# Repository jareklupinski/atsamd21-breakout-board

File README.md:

# atsamd21-breakout-board
A Boilerplate for the ATSAMD21 microcontroller

The ATSAMD21 is one of my favorite microcontroller families. Its low cost and ease of programming made me want to create a board that suits my project needs, so it contains RTC circuitry, an SD card slot, and a few other helpful dev touches.

The board was produced, plugged in, and did not emit magic smoke. All of the functionality hasn't been tested yet.

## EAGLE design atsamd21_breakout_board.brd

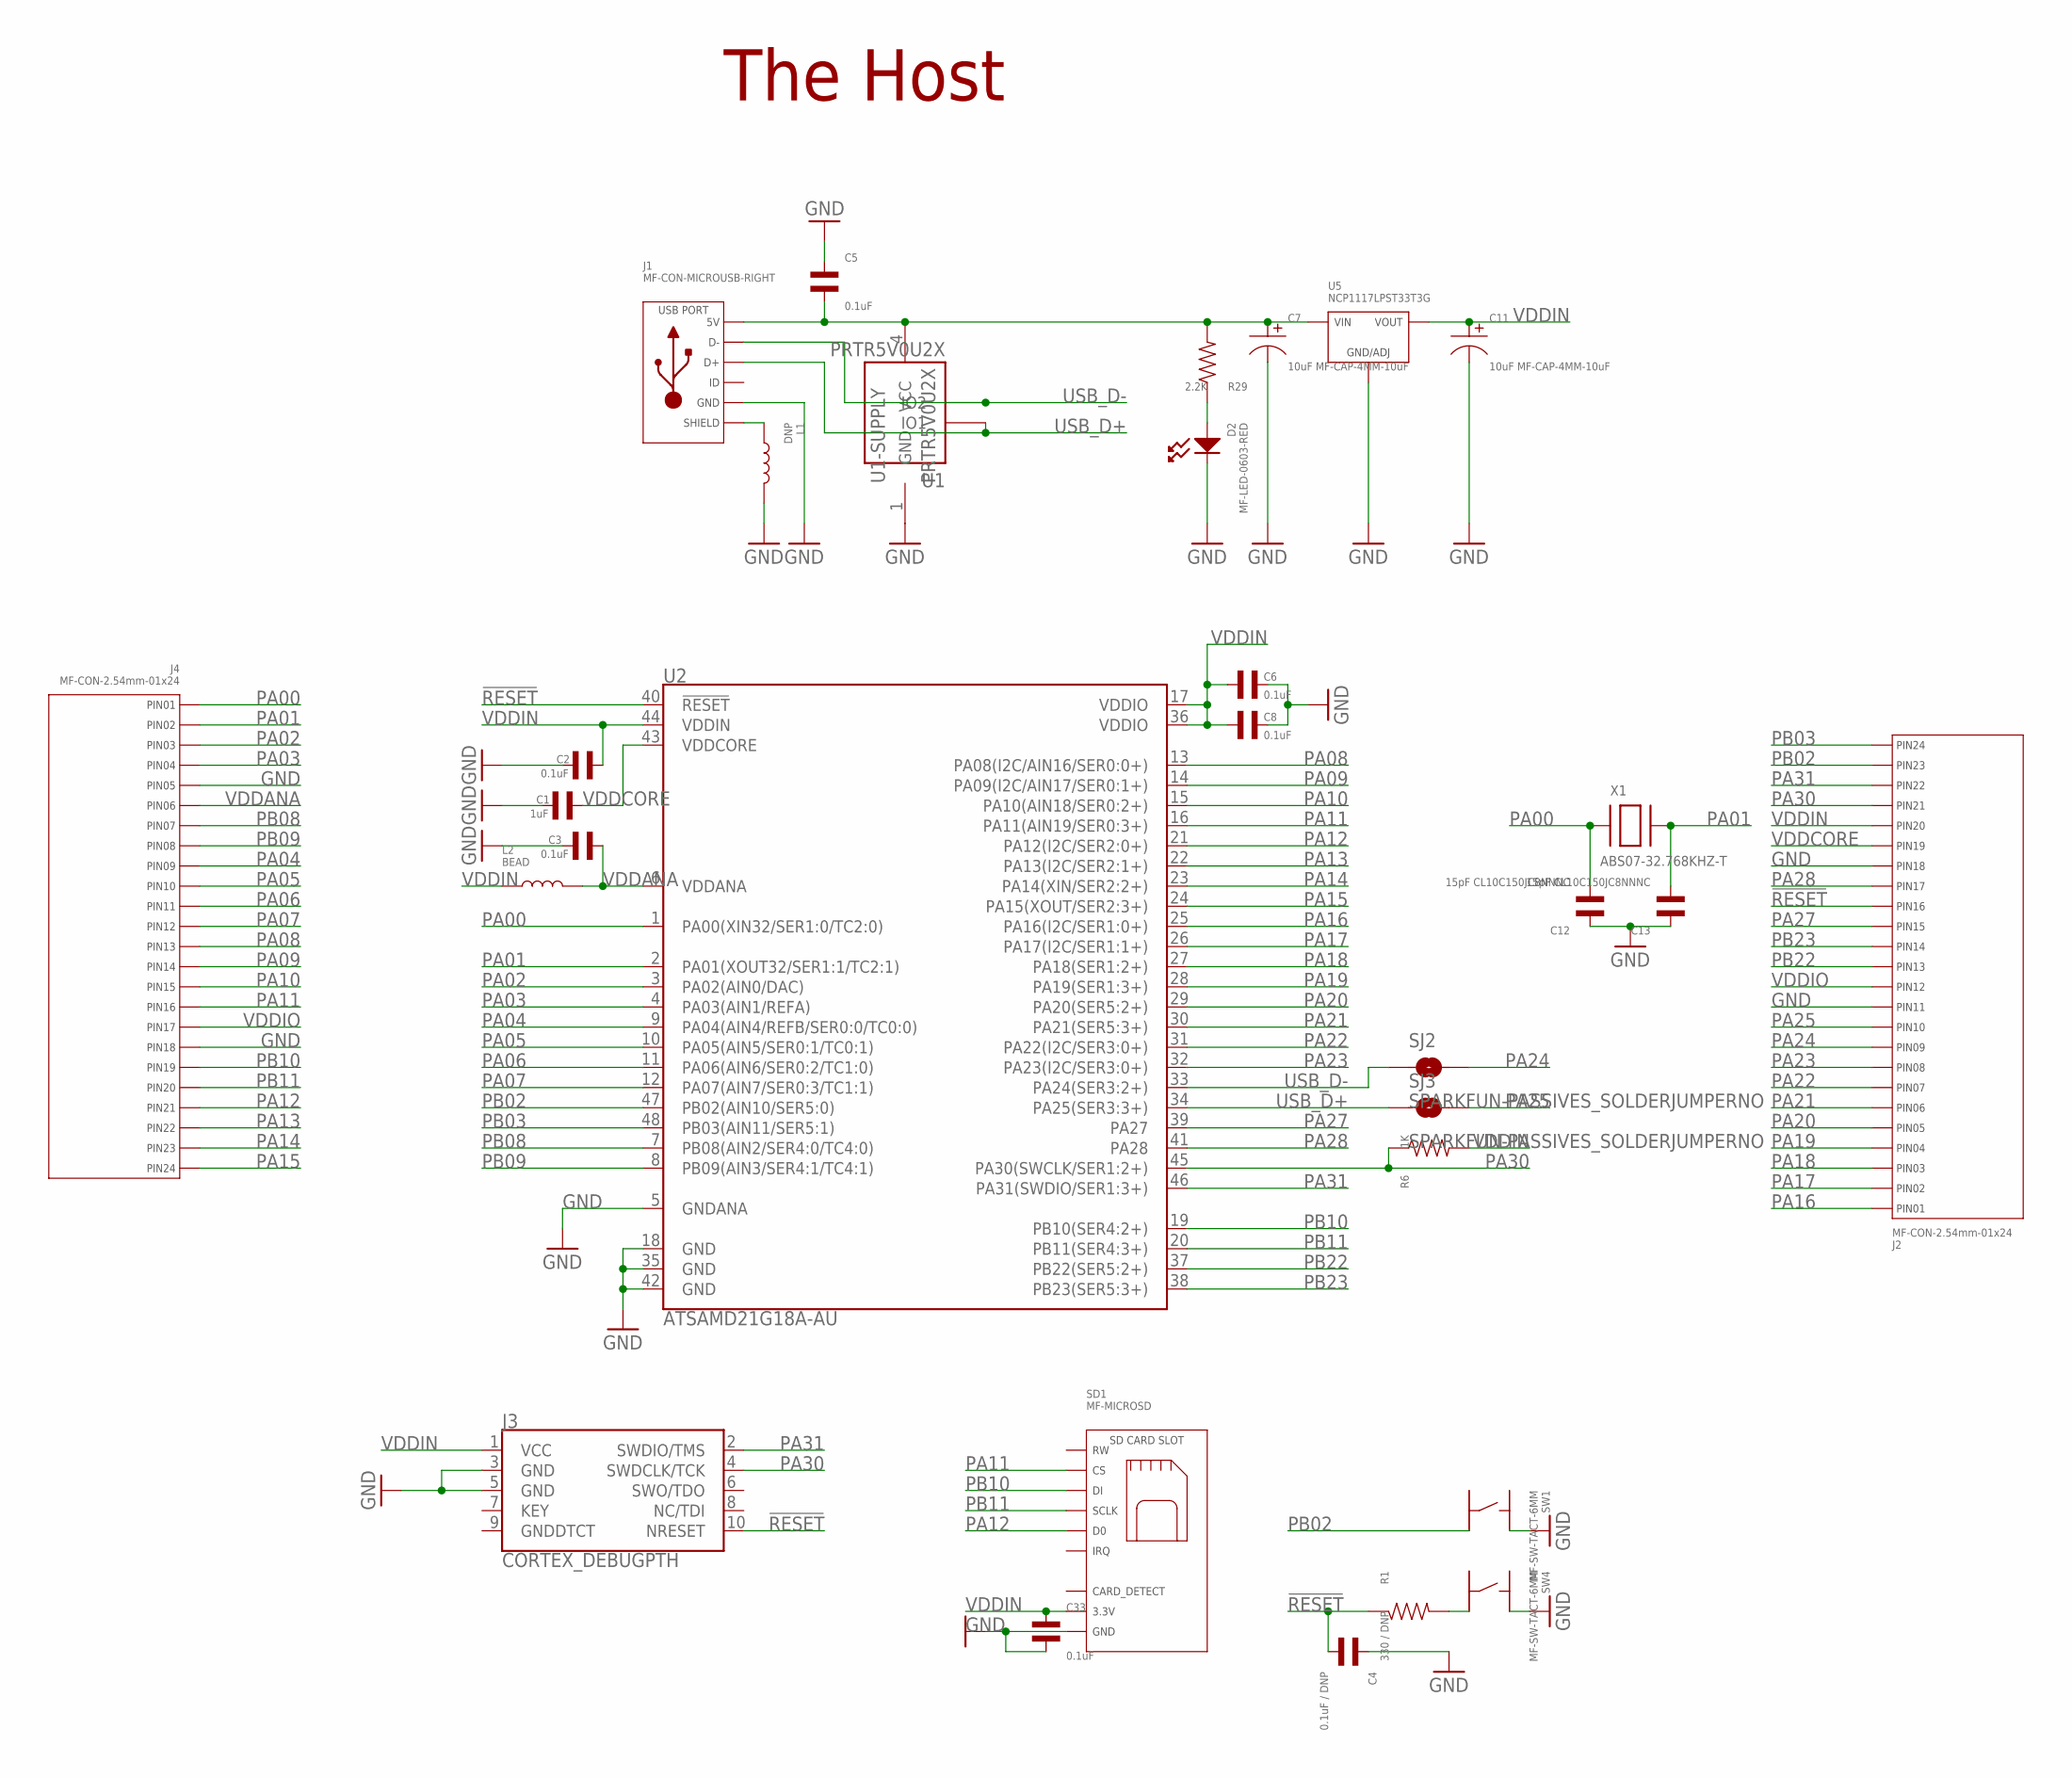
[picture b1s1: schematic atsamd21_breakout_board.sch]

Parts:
C1: 1uF; C0603
C2, C3, C5, C6, C8, C33: 0.1uF; C0603
C4: 0.1uF / DNP; C0603
C7, C11: 10uF MF-CAP-4MM-10uF; CP4MM
C12, C13: 15pF CL10C150JC8NNNC; C0603
D2: MF-LED-0603-RED; LED0603
J1: MF-CON-MICROUSB-RIGHT; MICROUSB-RIGHT
J2, J4: MF-CON-2.54mm-01x24; PTH_2.54MM_01X24
J3: CORTEX_DEBUGPTH; 2X5-PTH-1.27MM
L1: DNP; L1210
L2: BEAD; L1210
R1: 330 / DNP; R0603
R6: 1K; R0603
R29: 2.2K; R0603
SD1: MF-MICROSD
SJ2, SJ3: SPARKFUN-PASSIVES_SOLDERJUMPERNO; SPARKFUN-PASSIVES_SJ_2S-NO
SW1, SW4: MF-SW-TACT-6MM; TACT6MM
U1: PRTR5V0U2X; SOT-143B
U2: ATSAMD21G18A-AU; TQFP-48
U5: NCP1117LPST33T3G; SOT-223-3
X1: ABS07-32.768KHZ-T; XTAL3215

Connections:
!RESET: C4.P$2, J2.P$16 (PIN16), J3.10 (NRESET), R1.P$1, U2.40 (!RESET!)
GND: C1.P$2, C2.P$1, C3.P$1, C4.P$1, C5.P$1, C6.P$1, C7.P$2, C8.P$1, C11.P$2, C12.P$1, C13.P$1, C33.P$2, D2.CATHODE, J1.5 (GND), J2.P$11 (PIN11), J2.P$18 (PIN18), J3.3 (GND), J3.5 (GND), J4.P$5 (PIN5), J4.P$18 (PIN18), L1.P$2, SD1.G0 (GND), SD1.G1 (GND), SD1.PIN6 (GND), SW1.P$2, SW4.P$2, U1.1 (GND), U2.5 (GNDANA), U2.18 (GND), U2.35 (GND), U2.42 (GND), U5.P$2 (GND/ADJ)
unnamed: R1.P$2, SW4.P$4
unnamed: J1.S1 (SLD), J1.S2 (SLD), J1.S3 (SLD), J1.S4 (SLD), J1.S5 (SLD), J1.S6 (SLD), L1.P$1
unnamed: D2.ANODE, R29.P$1
unnamed: C5.P$2, C7.P$1, J1.1 (5V), R29.P$2, U1.4 (VCC), U5.P$4 (VIN)
PA00: C12.P$2, J4.P$1 (PIN1), U2.1 (PA00(XIN32/SER1:0/TC2:0)), X1.P$1
PA01: C13.P$2, J4.P$2 (PIN2), U2.2 (PA01(XOUT32/SER1:1/TC2:1)), X1.P$2
PA02: J4.P$3 (PIN3), U2.3 (PA02(AIN0/DAC))
PA03: J4.P$4 (PIN4), U2.4 (PA03(AIN1/REFA))
PA04: J4.P$9 (PIN9), U2.9 (PA04(AIN4/REFB/SER0:0/TC0:0))
PA05: J4.P$10 (PIN10), U2.10 (PA05(AIN5/SER0:1/TC0:1))
PA06: J4.P$11 (PIN11), U2.11 (PA06(AIN6/SER0:2/TC1:0))
PA07: J4.P$12 (PIN12), U2.12 (PA07(AIN7/SER0:3/TC1:1))
PA08: J4.P$13 (PIN13), U2.13 (PA08(I2C/AIN16/SER0:0+))
PA09: J4.P$14 (PIN14), U2.14 (PA09(I2C/AIN17/SER0:1+))
PA10: J4.P$15 (PIN15), U2.15 (PA10(AIN18/SER0:2+))
PA11: J4.P$16 (PIN16), SD1.PIN2 (CS), U2.16 (PA11(AIN19/SER0:3+))
PA12: J4.P$21 (PIN21), SD1.PIN7 (D0), U2.21 (PA12(I2C/SER2:0+))
PA13: J4.P$22 (PIN22), U2.22 (PA13(I2C/SER2:1+))
PA14: J4.P$23 (PIN23), U2.23 (PA14(XIN/SER2:2+))
PA15: J4.P$24 (PIN24), U2.24 (PA15(XOUT/SER2:3+))
PA16: J2.P$1 (PIN1), U2.25 (PA16(I2C/SER1:0+))
PA17: J2.P$2 (PIN2), U2.26 (PA17(I2C/SER1:1+))
PA18: J2.P$3 (PIN3), U2.27 (PA18(SER1:2+))
PA19: J2.P$4 (PIN4), U2.28 (PA19(SER1:3+))
PA20: J2.P$5 (PIN5), U2.29 (PA20(SER5:2+))
PA21: J2.P$6 (PIN6), U2.30 (PA21(SER5:3+))
PA22: J2.P$7 (PIN7), U2.31 (PA22(I2C/SER3:0+))
PA23: J2.P$8 (PIN8), U2.32 (PA23(I2C/SER3:0+))
PA24: J2.P$9 (PIN9), SJ2.2
PA25: J2.P$10 (PIN10), SJ3.2
PA27: J2.P$15 (PIN15), U2.39 (PA27)
PA28: J2.P$17 (PIN17), U2.41 (PA28)
PA30: J2.P$21 (PIN21), J3.4 (SWDCLK/TCK), R6.P$1, U2.45 (PA30(SWCLK/SER1:2+))
PA31: J2.P$22 (PIN22), J3.2 (SWDIO/TMS), U2.46 (PA31(SWDIO/SER1:3+))
PB02: J2.P$23 (PIN23), SW1.P$4, U2.47 (PB02(AIN10/SER5:0))
PB03: J2.P$24 (PIN24), U2.48 (PB03(AIN11/SER5:1))
PB08: J4.P$7 (PIN7), U2.7 (PB08(AIN2/SER4:0/TC4:0))
PB09: J4.P$8 (PIN8), U2.8 (PB09(AIN3/SER4:1/TC4:1))
PB10: J4.P$19 (PIN19), SD1.PIN3 (DI), U2.19 (PB10(SER4:2+))
PB11: J4.P$20 (PIN20), SD1.PIN5 (SCLK), U2.20 (PB11(SER4:3+))
PB22: J2.P$13 (PIN13), U2.37 (PB22(SER5:2+))
PB23: J2.P$14 (PIN14), U2.38 (PB23(SER5:3+))
USB_D+: J1.3 (D+), SJ3.1, U1.2 (IO1), U2.34 (PA25(SER3:3+))
USB_D-: J1.2 (D-), SJ2.1, U1.3 (IO2), U2.33 (PA24(SER3:2+))
VDDANA: C3.P$2, J4.P$6 (PIN6), L2.P$2, U2.6 (VDDANA)
VDDCORE: C1.P$1, J2.P$19 (PIN19), U2.43 (VDDCORE)
VDDIN: C2.P$2, C6.P$2, C8.P$2, C11.P$1, C33.P$1, J2.P$20 (PIN20), J3.1 (VCC), L2.P$1, R6.P$2, SD1.PIN4 (3.3V), U2.17 (VDDIO), U2.36 (VDDIO), U2.44 (VDDIN), U5.P$1 (VOUT), U5.P$3 (VOUT)
VDDIO: J2.P$12 (PIN12), J4.P$17 (PIN17)

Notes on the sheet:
The Host

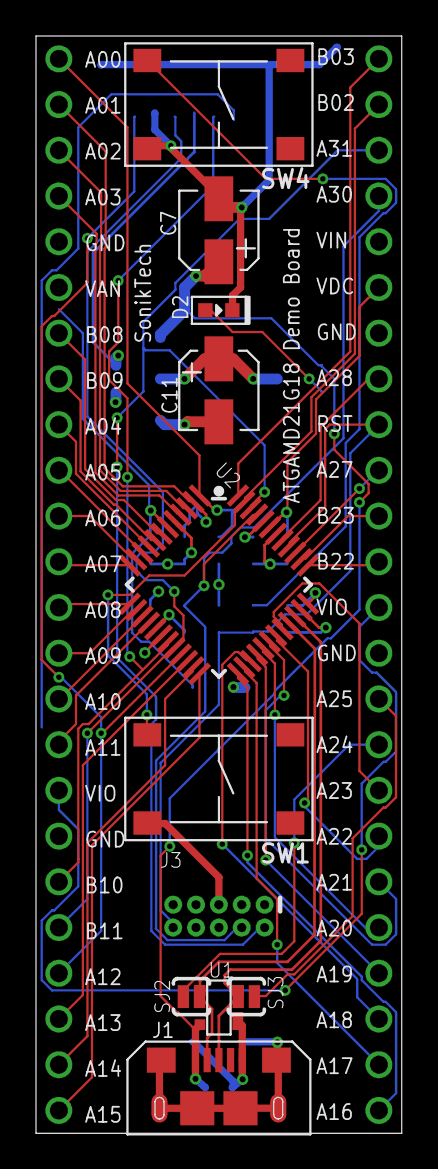
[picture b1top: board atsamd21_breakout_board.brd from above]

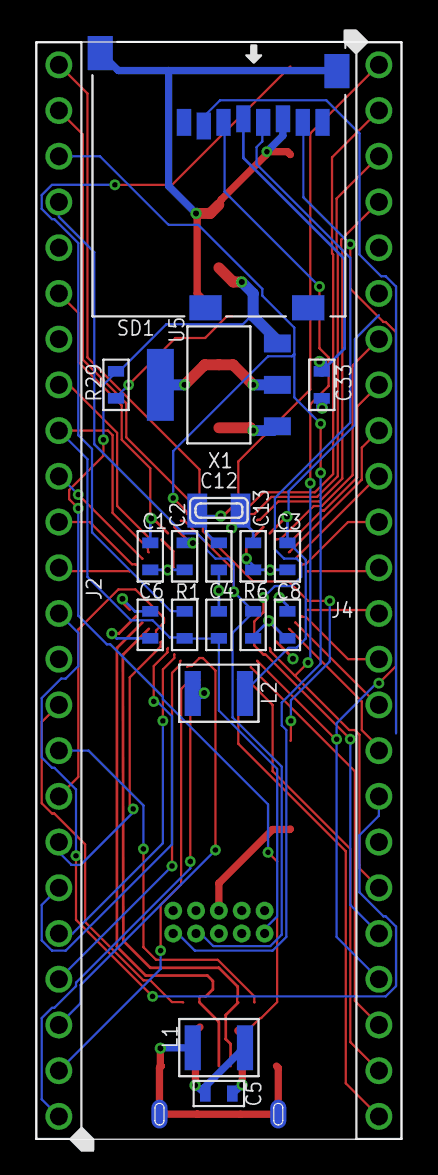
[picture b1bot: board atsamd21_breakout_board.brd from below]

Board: 4 copper layers, 20.3 x 60.9 mm, 31 parts (20 on the bottom side), 50 nets.

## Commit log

2018-07-04 design produced: untested

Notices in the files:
parts and their libraries:
SparkFun-Connectors: Licensing: Creative Commons ShareAlike 4.0 International - https://creativecommons.org/licenses/by-sa/4.0
Volks73-NXPSemiconductors: Creative Commons Attribution-ShareAlike 3.0 Unported (CC BY-SA 3.0), http://creativecommons.org/licenses/by-sa/3.0/.
